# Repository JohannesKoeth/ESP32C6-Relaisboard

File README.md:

# ESP32C6-Relaisboard
ESP32C6 based relais board with RS485 interface

# Mistake in Schematics

The RS485 pins are connected to the wrong ESP32 pins and I could not get the communication working

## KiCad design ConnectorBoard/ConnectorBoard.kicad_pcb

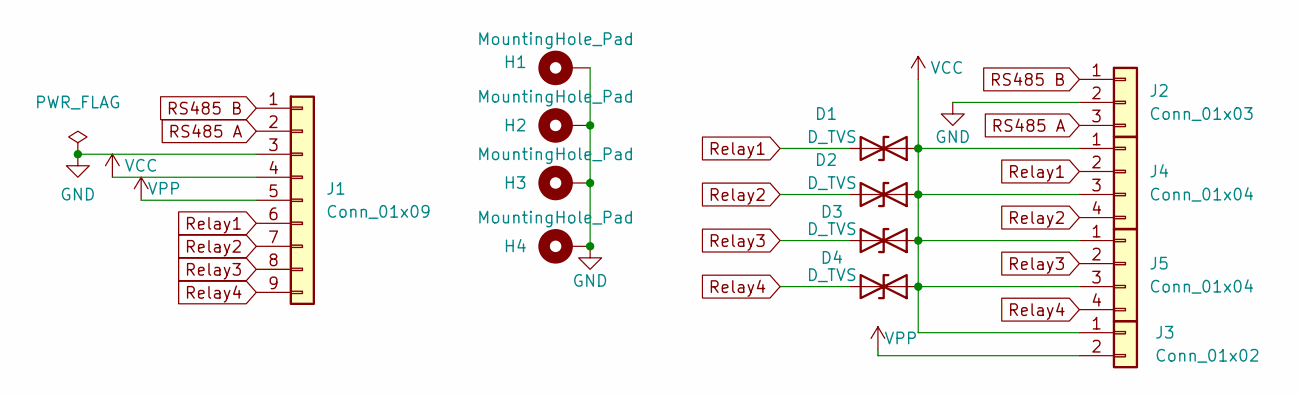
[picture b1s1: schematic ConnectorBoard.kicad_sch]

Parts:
D1, D2, D3, D4: D_TVS; D_SOD-323
H1, H2, H3, H4: MountingHole_Pad; MountingHole_3.2mm_M3_Pad_Via
J1: Conn_01x09; JST_PH_B9B-PH-K_1x09_P2.00mm_Vertical
J2: Conn_01x03; CUI_TB001-500-03BE
J3: Conn_01x02; CUI_TB001-500-02BE
J4, J5: Conn_01x04; CUI_TB001-500-04BE

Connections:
GND: H1.1, H2.1, H3.1, H4.1, J1.3, J2.2
RS485 A: J1.2, J2.3
RS485 B: J1.1, J2.1
Relay1: D1.2 (A2), J1.6, J4.2
Relay2: D2.2 (A2), J1.7, J4.4
Relay3: D3.2 (A2), J1.8, J5.2
Relay4: D4.2 (A2), J1.9, J5.4
VCC: D1.1 (A1), D2.1 (A1), D3.1 (A1), D4.1 (A1), J1.4, J3.1, J4.1, J4.3, J5.1, J5.3
VPP: J1.5, J3.2

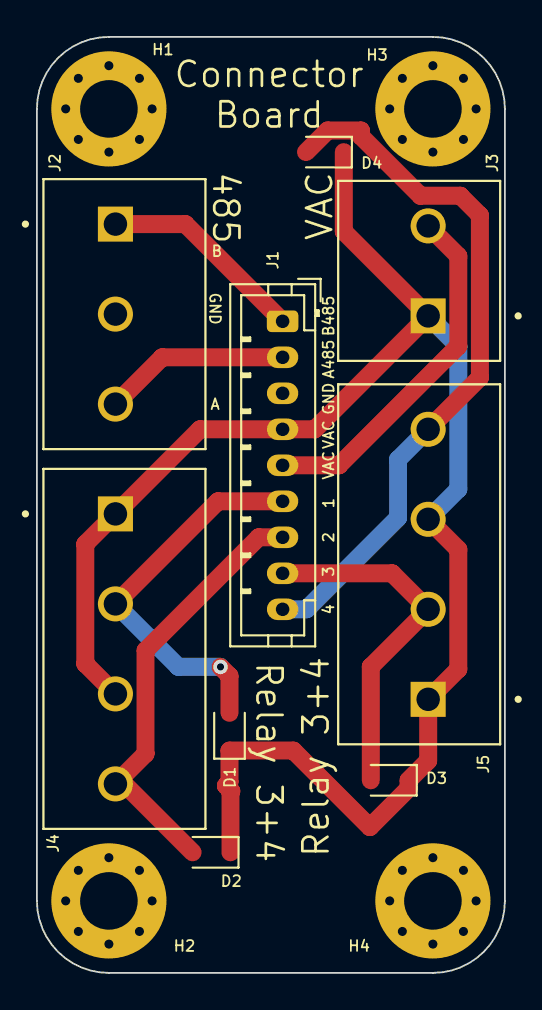
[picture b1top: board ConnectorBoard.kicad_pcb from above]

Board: 2 copper layers, 26.0 x 52.0 mm, 13 parts (0 on the bottom side), 9 nets.

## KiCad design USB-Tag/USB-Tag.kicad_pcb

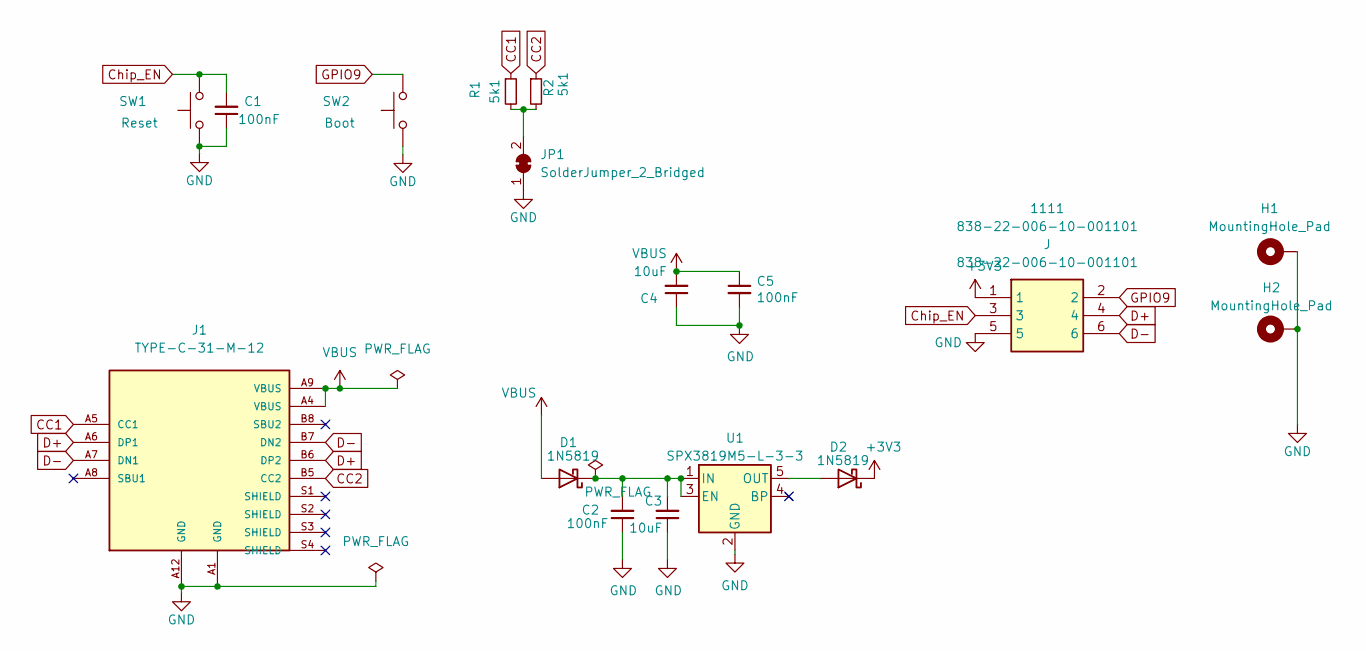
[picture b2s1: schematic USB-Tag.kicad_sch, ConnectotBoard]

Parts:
1111: 838-22-006-10-001101; HDRV6W56P200_2X3_600X400X749P; Mouser Part Number 575-8382200610001101
C1, C2, C5: 100nF; C_0402_1005Metric; LCSC Part # C1525
C3, C4: 10uF; C_0402_1005Metric; LCSC Part # C15525
D1, D2: 1N5819; D_SOD-323; LCSC Part # C191023
H1, H2: MountingHole_Pad; MountingHole_3.5mm_Pad_Via
J1: TYPE-C-31-M-12; HRO_TYPE-C-31-M-12; PARTREV 2020.12.08; LCSC Part # C165948
JP1: SolderJumper_2_Bridged; SolderJumper-2_P1.3mm_Bridged_RoundedPad1.0x1.5mm
R1, R2: 5k1; R_0402_1005Metric; LCSC Part # C105872
SW1: Reset; SW_PUSH_6mm
SW2: Boot; SW_PUSH_6mm
U1: SPX3819M5-L-3-3; SOT-23-5; LCSC Part # C9055

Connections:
+3V3: 1111.1, D2.1 (K)
CC1: J1.A5 (CC1), R1.1
CC2: J1.B5 (CC2), R2.1
Chip_EN: 1111.3, C1.2, SW1.2
D+: 1111.4, J1.A6 (DP1), J1.B6 (DP2)
D-: 1111.6, J1.A7 (DN1), J1.B7 (DN2)
GND: 1111.5, C1.1, C2.1, C3.1, C4.1, C5.2, H1.1, H2.1, J1.A1 (GND), J1.A12 (GND), JP1.1 (A), SW1.1, SW2.1, U1.2 (GND)
GPIO9: 1111.2, SW2.2
unnamed: C2.2, C3.2, D1.1 (K), U1.1 (IN), U1.3 (EN)
unnamed: D2.2 (A), U1.5 (OUT)
unnamed: JP1.2 (B), R1.2, R2.2
VBUS: C4.2, C5.1, D1.2 (A), J1.A4 (VBUS), J1.A9 (VBUS)

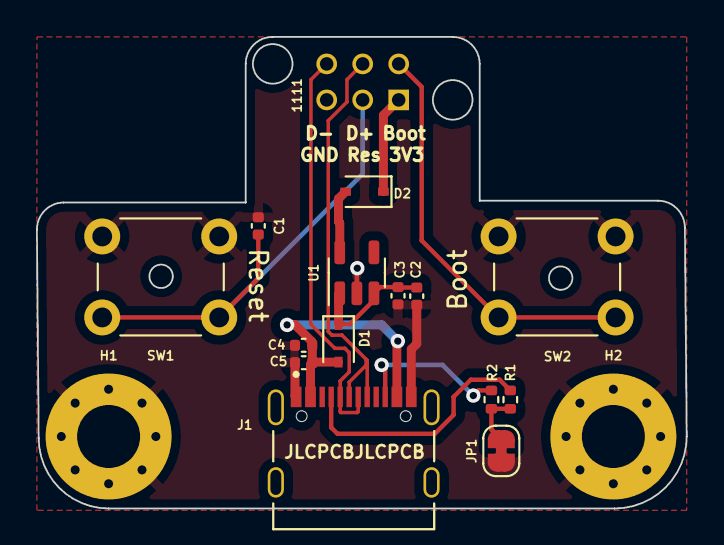
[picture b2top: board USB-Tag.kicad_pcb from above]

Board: 2 copper layers, 36.1 x 26.2 mm, 17 parts (1 on the bottom side), 12 nets.

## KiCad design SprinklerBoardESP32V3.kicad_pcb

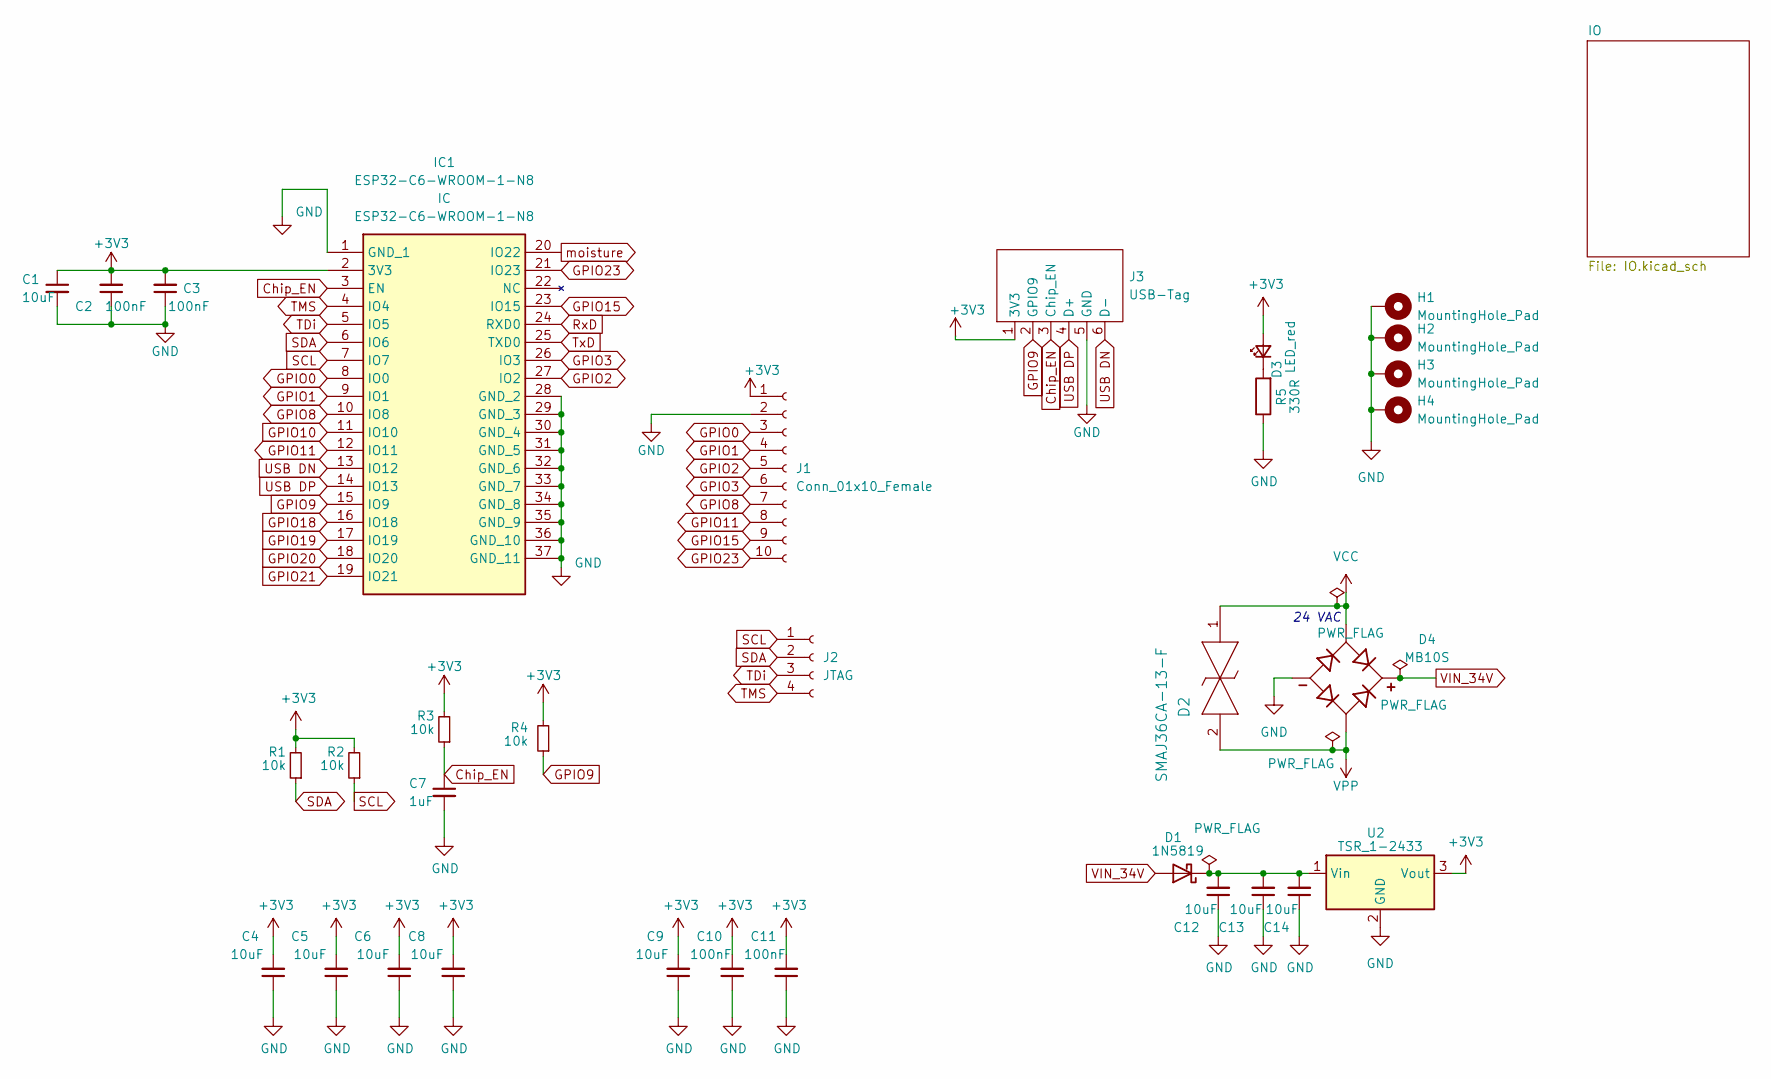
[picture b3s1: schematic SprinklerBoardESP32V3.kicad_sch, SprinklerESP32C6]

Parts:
C1: 10uF; C_0402_1005Metric; LCSC Part# C15525
C2, C3, C10, C11: 100nF; C_0402_1005Metric; LCSC Part # C1525
C4, C5, C6, C8, C9, C12, C13, C14: 10uF; C_0402_1005Metric; LCSC Part # C15525
C7: 1uF; C_0402_1005Metric; LCSC Part # C167339
D1: 1N5819; D_SOD-323; LCSC Part # C191023
D2: SMAJ36CA-13-F; D_SMA; LCSC Part # C10757
D3: LED_red; LED_0402_1005Metric; LCSC Part # C434449
D4: MB10S; SOIC245P670X290-4N; LCSC Part # C2488
H1, H2, H3, H4: MountingHole_Pad; MountingHole_3.2mm_M3_Pad_Via
IC1: ESP32-C6-WROOM-1-N8; ESP32C6WROOM1N8; Manufacturer_Part_Number ESP32-C6-WROOM-1-N8; Mouser Part Number 356-ESP32C6WROOM1N8
J1: Conn_01x10_Female; PinHeader_2x05_P2.00mm_Vertical_SMD
J2: JTAG; PinHeader_1x04_P2.00mm_Vertical
J3: USB-Tag; USB-Tag_6pol
R1, R2, R3, R4: 10k; R_0402_1005Metric; LCSC Part # C25744
R5: 330R; R_0402_1005Metric; LCSC Part # C25104
U2: TSR_1-2433; Converter_DCDC_TRACO_TSR-1_THT

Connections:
Chip_EN: C7.1, IC1.3 (EN), J3.3 (Chip_EN), R3.1
GPIO0: IC1.8 (IO0), J1.3
GPIO1: IC1.9 (IO1), J1.4
GPIO2: IC1.27 (IO2), J1.5
GPIO3: IC1.26 (IO3), J1.6
GPIO8: IC1.10 (IO8), J1.7
GPIO9: IC1.15 (IO9), J3.2 (GPIO9), R4.1
GPIO11: IC1.12 (IO11), J1.8
GPIO15: IC1.23 (IO15), J1.9
GPIO18: IC1.16 (IO18); also elsewhere on the board
GPIO19: IC1.17 (IO19); also elsewhere on the board
GPIO20: IC1.18 (IO20); also elsewhere on the board
GPIO21: IC1.19 (IO21); also elsewhere on the board
GPIO23: IC1.21 (IO23), J1.10
unnamed: D3.1 (K), R5.2
unnamed 24: U2.7 (B); also elsewhere on the board
unnamed 25: U2.6 (A); also elsewhere on the board
SCL: IC1.7 (IO7), J2.1, R2.1; also elsewhere on the board
SDA: IC1.6 (IO6), J2.2, R1.1; also elsewhere on the board
TDi: IC1.5 (IO5), J2.3
TMS: IC1.4 (IO4), J2.4
TxD: IC1.25 (TXD0), U2.4 (DI)
USB DN: IC1.13 (IO12), J3.6 (D-)
USB DP: IC1.14 (IO13), J3.4 (D+)
VCC: D2.1 (K), D4.3; also elsewhere on the board
VIN_34V: D1.2 (A), D4.1
VPP: D2.2 (A), D4.4; also elsewhere on the board
moisture: IC1.20 (IO22); also elsewhere on the board

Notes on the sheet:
24 VAC

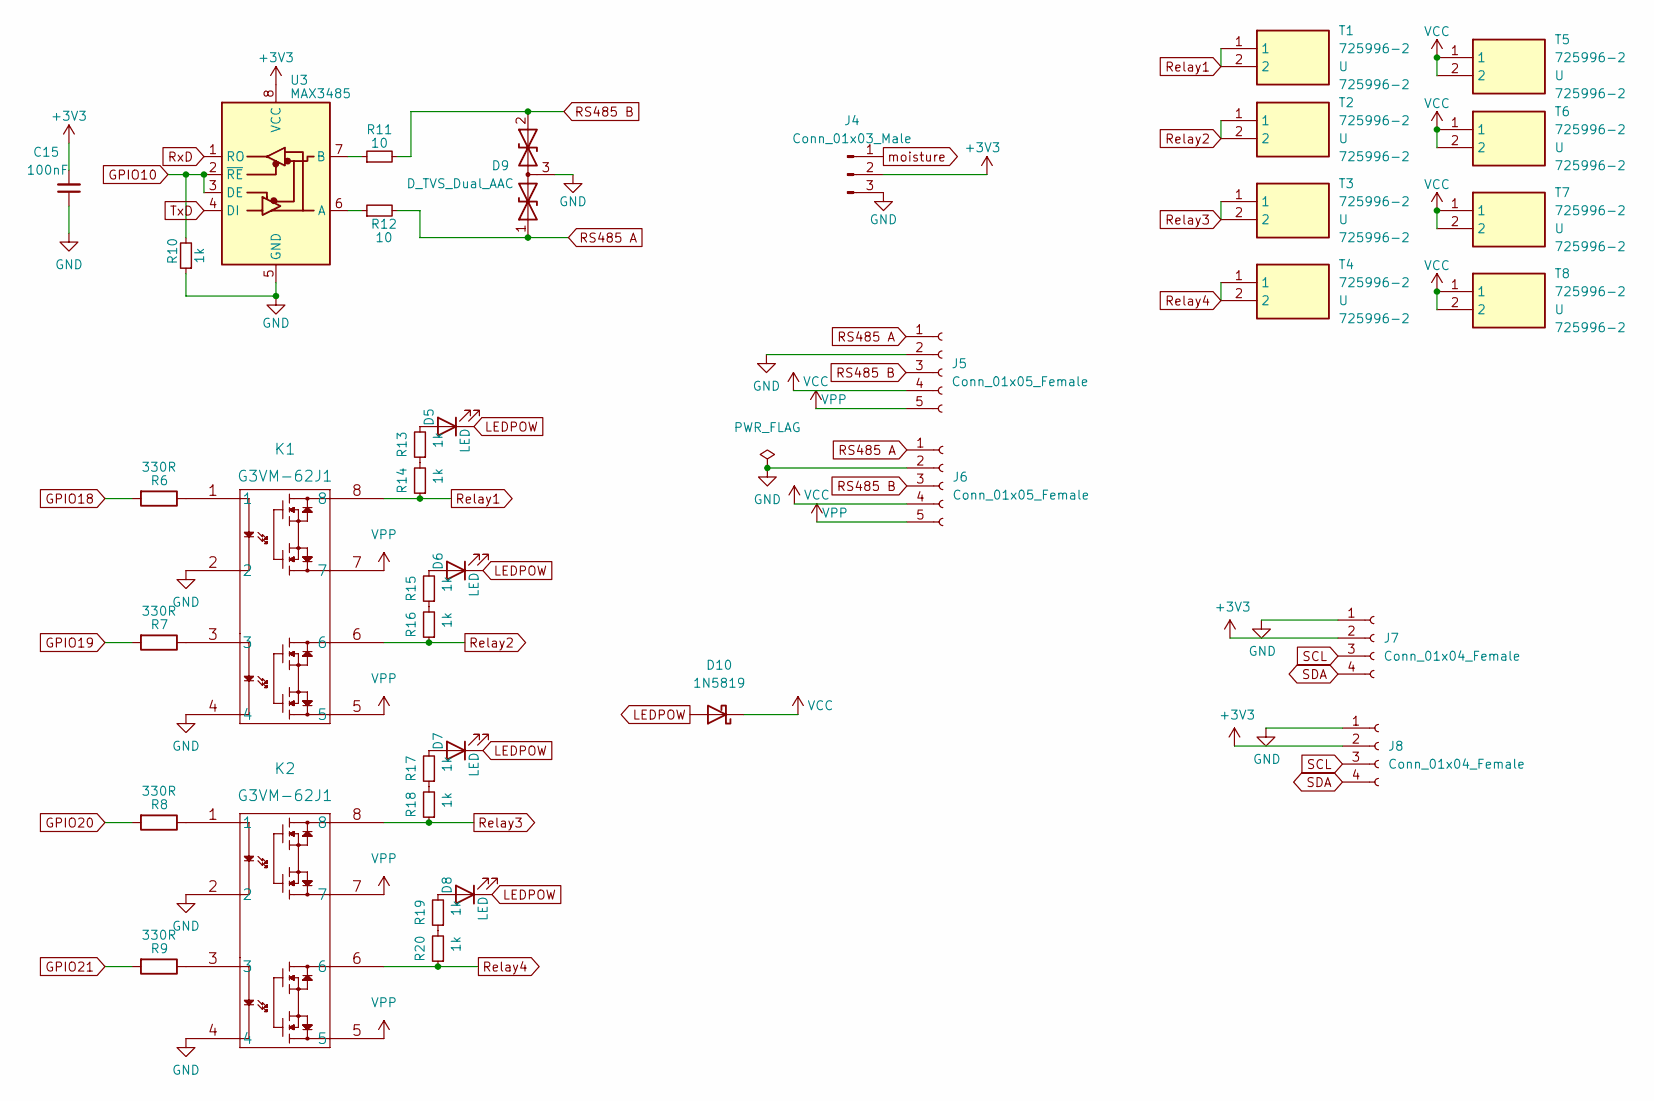
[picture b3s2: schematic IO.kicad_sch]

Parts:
C15: 100nF; C_0402_1005Metric; LCSC Part # C1525
D5, D6, D7, D8: LED; LED_0402_1005Metric; LCSC Part # C130724
D9: D_TVS_Dual_AAC; SOT-23; LCSC Part # C32677
D10: 1N5819; D_SOD-323; LCSC Part # C191023
J4: Conn_01x03_Male; JST_PH_B3B-PH-K_1x03_P2.00mm_Vertical
J5, J6: Conn_01x05_Female; PinSocket_1x05_P2.54mm_Vertical
J7: Conn_01x04_Female; JST_PH_B4B-PH-SM4-TB_1x04-1MP_P2.00mm_Vertical
J8: Conn_01x04_Female; PinSocket_1x04_P2.54mm_Vertical
K1, K2: G3VM-62J1; J-SOP8_OMR; LCSC Part # C726024
R6, R7, R8, R9: 330R; R_0402_1005Metric; LCSC Part # C25104
R10, R13, R14, R15, R16, R17, R18, R19, R20: 1k; R_0402_1005Metric; LCSC Part # C11702
R11, R12: 10; R_0402_1005Metric; LCSC Part # C25077
T1, T2, T3, T4, T5, T6, T7, T8: 725996-2; 7259962; Manufacturer_Part_Number 725996-2; Mouser Part Number 571-725996-2
U3: MAX3485; SOIC-8_3.9x4.9mm_P1.27mm; LCSC Part # C18148

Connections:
GPIO18: R6.2; also elsewhere on the board
GPIO19: R7.2; also elsewhere on the board
GPIO20: R8.2; also elsewhere on the board
GPIO21: R9.2; also elsewhere on the board
LEDPOW: D5.1 (K), D6.1 (K), D7.1 (K), D8.1 (K), D10.2 (A)
unnamed: D5.2 (A), R13.2
unnamed: D6.2 (A), R15.2
unnamed: D7.2 (A), R17.2
unnamed: D8.2 (A), R19.2
unnamed: K1.1, R6.1
unnamed: K1.3, R7.1
unnamed: K2.1, R8.1
unnamed: K2.3, R9.1
unnamed 24: R11.1, U3.7 (B); also elsewhere on the board
unnamed 25: R12.1, U3.6 (A); also elsewhere on the board
unnamed: R13.1, R14.2
unnamed: R15.1, R16.2
unnamed: R17.1, R18.2
unnamed: R19.1, R20.2
RS485 A: D9.1 (A1), J5.1, J6.1, R12.2
RS485 B: D9.2 (A2), J5.3, J6.3, R11.2
Relay1: K1.8, R14.1, T1.1, T1.2
Relay2: K1.6, R16.1, T2.1, T2.2
Relay3: K2.8, R18.1, T3.1, T3.2
Relay4: K2.6, R20.1, T4.1, T4.2
SCL: J7.3, J8.3; also elsewhere on the board
SDA: J7.4, J8.4; also elsewhere on the board
VCC: D10.1 (K), J5.4, J6.4, T5.1, T5.2, T6.1, T6.2, T7.1, T7.2, T8.1, T8.2; also elsewhere on the board
VPP: J5.5, J6.5, K1.5, K1.7, K2.5, K2.7; also elsewhere on the board
moisture: J4.1; also elsewhere on the board

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
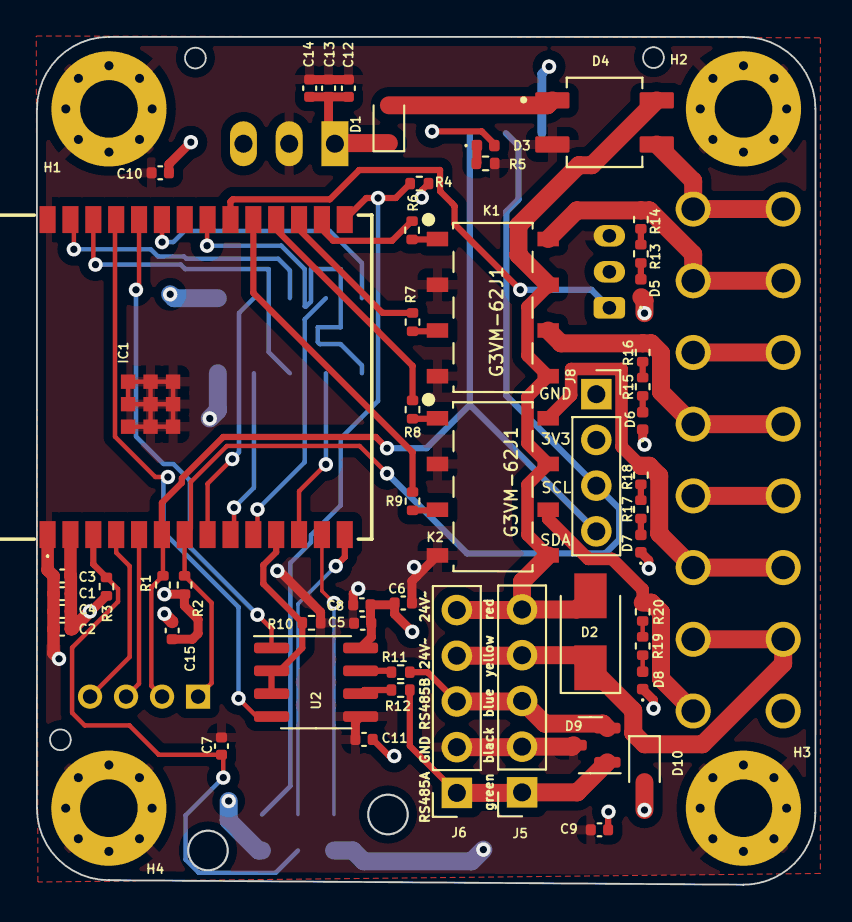
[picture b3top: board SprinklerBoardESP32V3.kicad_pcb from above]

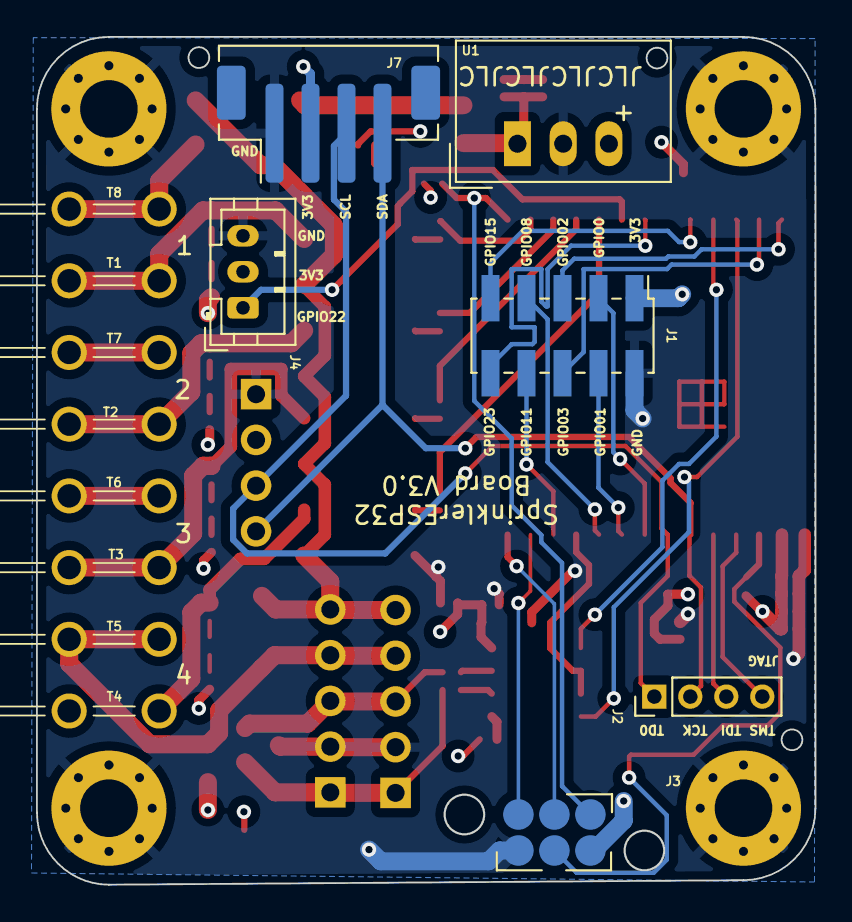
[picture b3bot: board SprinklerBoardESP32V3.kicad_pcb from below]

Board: 4 copper layers, 43.2 x 47.1 mm, 70 parts (14 on the bottom side), 52 nets.

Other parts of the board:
U1: TSR_1-2433; Converter_DCDC_TRACO_TSR-1_THT

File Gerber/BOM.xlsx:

Comment | Designator | Footprint | LCSC Partn Number
10uF | C1 | Capacitor_SMD:C_0402_1005Metric | C15525
100nF | C2 | Capacitor_SMD:C_0402_1005Metric | C1525
100nF | C3 | Capacitor_SMD:C_0402_1005Metric | C1525
10uF | C4 | Capacitor_SMD:C_0402_1005Metric | C15525
10uF | C5 | Capacitor_SMD:C_0402_1005Metric | C15525
10uF | C6 | Capacitor_SMD:C_0402_1005Metric | C15525
1uF | C7 | Capacitor_SMD:C_0402_1005Metric | C167339
10uF | C8 | Capacitor_SMD:C_0402_1005Metric | C15525
10uF | C9 | Capacitor_SMD:C_0402_1005Metric | C15525
100nF | C10 | Capacitor_SMD:C_0402_1005Metric | C1525
100nF | C11 | Capacitor_SMD:C_0402_1005Metric | C1525
10uF | C12 | Capacitor_SMD:C_0402_1005Metric | C15525
10uF | C13 | Capacitor_SMD:C_0402_1005Metric | C15525
10uF | C14 | Capacitor_SMD:C_0402_1005Metric | C15525
100nF | C15 | Capacitor_SMD:C_0402_1005Metric | C1525
1N5819 | D1 | Diode_SMD:D_SOD-323 | C191023
SMAJ36CA-13-F | D2 | Diode_SMD:D_SMA | C10757
LED_red | D3 | LED_SMD:LED_0402_1005Metric | C434449
MB10S | D4 | MB10S:SOIC245P670X290-4N | C2488
LED | D5 | LED_SMD:LED_0402_1005Metric | C130724
LED | D6 | LED_SMD:LED_0402_1005Metric | C130724
LED | D7 | LED_SMD:LED_0402_1005Metric | C130724
LED | D8 | LED_SMD:LED_0402_1005Metric | C130724
D_TVS_Dual_AAC | D9 | Package_TO_SOT_SMD:SOT-23 | C32677
1N5819 | D10 | Diode_SMD:D_SOD-323 | C191023
MountingHole_Pad | H1 | MountingHole:MountingHole_3.2mm_M3_Pad_Via
MountingHole_Pad | H2 | MountingHole:MountingHole_3.2mm_M3_Pad_Via
MountingHole_Pad | H3 | MountingHole:MountingHole_3.2mm_M3_Pad_Via
MountingHole_Pad | H4 | MountingHole:MountingHole_3.2mm_M3_Pad_Via
ESP32-C6-WROOM-1-N8 | IC1 | ESP32-C6:ESP32C6WROOM1N8
Conn_01x10_Female | J1 | Connector_PinHeader_2.00mm:PinHeader_2x05_P2.00mm_Vertical_SMD
JTAG | J2 | Connector_PinHeader_2.00mm:PinHeader_1x04_P2.00mm_Vertical
USB-Tag | J3 | USB-Tag:USB-Tag_6pol
Conn_01x03_Male | J4 | Connector_JST:JST_PH_B3B-PH-K_1x03_P2.00mm_Vertical
Conn_01x05_Female | J5 | Connector_PinSocket_2.54mm:PinSocket_1x05_P2.54mm_Vertical
Conn_01x05_Female | J6 | Connector_PinSocket_2.54mm:PinSocket_1x05_P2.54mm_Vertical
Conn_01x04_Female | J7 | Connector_JST:JST_PH_B4B-PH-SM4-TB_1x04-1MP_P2.00mm_Vertical
Conn_01x04_Female | J8 | Connector_PinSocket_2.54mm:PinSocket_1x04_P2.54mm_Vertical
G3VM-62J1 | K1 | J-SOP8_OMR | C726024
G3VM-62J1 | K2 | J-SOP8_OMR | C726024
10k | R1 | Resistor_SMD:R_0402_1005Metric | C25744
10k | R2 | Resistor_SMD:R_0402_1005Metric | C25744
10k | R3 | Resistor_SMD:R_0402_1005Metric | C25744
10k | R4 | Resistor_SMD:R_0402_1005Metric | C25744
330R | R5 | Resistor_SMD:R_0402_1005Metric | C25104
330R | R6 | Resistor_SMD:R_0402_1005Metric | C25104
330R | R7 | Resistor_SMD:R_0402_1005Metric | C25104
330R | R8 | Resistor_SMD:R_0402_1005Metric | C25104
330R | R9 | Resistor_SMD:R_0402_1005Metric | C25104
1k | R10 | Resistor_SMD:R_0402_1005Metric | C11702
10 | R11 | Resistor_SMD:R_0402_1005Metric | C25077
10 | R12 | Resistor_SMD:R_0402_1005Metric | C25077
1k | R13 | Resistor_SMD:R_0402_1005Metric | C11702
1k | R14 | Resistor_SMD:R_0402_1005Metric | C11702
1k | R15 | Resistor_SMD:R_0402_1005Metric | C11702
1k | R16 | Resistor_SMD:R_0402_1005Metric | C11702
1k | R17 | Resistor_SMD:R_0402_1005Metric | C11702
1k | R18 | Resistor_SMD:R_0402_1005Metric | C11702
1k | R19 | Resistor_SMD:R_0402_1005Metric | C11702
1k | R20 | Resistor_SMD:R_0402_1005Metric | C11702
725996-2 | T1 | 725996:7259962
725996-2 | T2 | 725996:7259962
725996-2 | T3 | 725996:7259962
725996-2 | T4 | 725996:7259962
725996-2 | T5 | 725996:7259962
725996-2 | T6 | 725996:7259962
725996-2 | T7 | 725996:7259962
725996-2 | T8 | 725996:7259962
TSR_1-2433 | U1 | Converter_DCDC:Converter_DCDC_TRACO_TSR-1_THT
MAX3485+A2AA3:A71 | U2 | Package_SO:SOIC-8_3.9x4.9mm_P1.27mm | C18148

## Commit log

2023-07-31 Added Timer in MCU program
2023-07-31 Added MCU Software
2023-07-31 Put the RS485 code into seperate file
2023-07-31 Added image files
2023-08-02 Added #if for use without display
2023-08-02 Added testroutine for relais
2023-08-03 Fixed output to screen

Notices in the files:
parts and their libraries:
Copyright 2021 Accelerated Designs. All rights reserved.
